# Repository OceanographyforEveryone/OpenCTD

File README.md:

# OpenCTD Rev8 is here!

**The ocean belongs to everyone.** The tools to study the ocean should be accessible to anyone with the curiosity and motivation to pursue that inquiry. Build your own [research-quality oceanographic instrument](https://tos.org/oceanography/article/the-openctd-a-low-cost-open-source-ctd-for-collecting-baseline-oceanographic-data-in-coastal-waters) and let's explore the ocean, together. 

# OpenCTD: Oceanography for Everyone

The CTD is an oveanographic instrument that measures salinity, temperature, and depth. By measuring these
characteristics, scientists can begin to unlock ocean patterns hidden beneath the sea's surface.

CTDs come in a variety of shapes, sizes, and applications. Most oceanographic research vessels have a CTD connected to a rosette platform, which houses other instruments and collects water samples in parallel with real-time data. CTDs are also commonly attached to fixed moorings, autonomous underwater vehicles (AUVs), remote-operated vehicles (ROVs), and even to marine animals.

Unfortunately, commercial CTDs are expensive. The most affordable models cost several thousand dollars. For near-shore oceanographic research on the relatively shallow continental shelf, this cost can be prohibitive. This
effectively excludes formal researchers from low and middle income countries, and small island states. Even in high-income countries, formal researchers at teaching institutions or at early career stages may also find themselves priced out of ocean research. Informal researchers such as citizen oceanographers, educators, conservation and management practitioners and students of all levels face severe challenges accessing expensive scientific instruments. 

**You don’t need to ask for permission to understand your world.**

By building your own instruments to study and understand the natural world, you are expanding the circle of knowledge production. A scientist who can make their own instruments is not beholden to the cycles of funding and access that constrain formal, institutional inquiry. A researcher who can build and repair their own equipment is not dependent on the whims of academic sentiment to decide what is and is not worthy of study. A community leader who has the tools to create their own data does not have to wait for institutions to take notice
of an emerging crisis before taking action. 

.jpg)

### Build Your Own CTD

The OpenCTD is a low-cost, open-source CTD designed for budget-restricted
scientists, educators, and researchers working in nearshore coastal ecosystems.
In these waterways, entire research projects can be conducted for less than the
cost of a commercial CTD. OpenCTD was developed by a core team of marine
ecologists in collaboration with a community of scientists, engineers, makers,
and conservation practitioners from around the world. It is assembled from
components commonly available at large hardware stores or through major online
retailers. An Arduino-based microcontroller controls an array of sensors sealed
within a PVC pipe. Power is provided by a standard 3.7V lithium polymer battery
and data are stored in a tab-delimited text file accessed via SD card.  All
OpenCTD software is released open source with no restrictions on use. 

The OpenCTD built by the end-user, providing both access to
the tools of oceanography as well as the skills to maintain, repair, and
replace OpenCTDs. For scientists working in remote settings, the repairability
of the OpenCTD is intended to prevent equipment failures from spiraling into
project failures. For educators seeking novel, in-depth, hands-on STEM
experience for advanced students, the process of building an OpenCTD offers an
introduction to coding, 3D-printing, hardware prototyping, and electronics.
Construction of an OpenCTD can provide a practical foundation for courses in
oceanography and marine or environmental science. 

# Visit [Oceanography for Everyone](http://oceanographyforeveryone.com/) to learn more, inquire about workshops, or purchase OpenCTD kits!

### Publications

Thaler, A., S.K. Sturdivant, R.Y. Neches, and J.J. Levenson. 2024. [The OpenCTD: A low-cost, open-source CTD for collecting baseline oceanographic data in coastal waters](https://tos.org/oceanography/article/the-openctd-a-low-cost-open-source-ctd-for-collecting-baseline-oceanographic-data-in-coastal-waters#citation). Oceanography 37(2):167–173, https://doi.org/10.5670/oceanog.2024.602.

### Core Resources

The [OpenCTD Construction and
Operation](https://github.com/OceanographyforEveryone/OpenCTD/tree/main/Documentation)
manual provides a comprehensive, step-by-step guide to building your own
OpenCTD, with a standard construction pathway as well as numerous alternatives
depending on parts availability and technical skills. A shorter manual covering just the calibration process is also available. 

The OpenCTD [core software](https://github.com/OceanographyforEveryone/OpenCTD/tree/main/Software) is designed
to be used with an M0-style Arduino microcontroller, for which we recommend the
[Adafruit Adalogger Feather M0](https://www.adafruit.com/product/2796). 

You can find all the Arduino libraries as described in the manual, as well as
software for calibrating the conductivity sensors in
[Support](https://github.com/OceanographyforEveryone/OpenCTD/tree/main/Software/Support).

Hardware file for both 3D printable components and the control unit PBC can be found in [Hardware](https://github.com/OceanographyforEveryone/OpenCTD/tree/main/Hardware)

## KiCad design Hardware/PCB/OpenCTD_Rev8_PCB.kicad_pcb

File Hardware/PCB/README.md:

# OpenCTD PCB

The OpenCTD main board is designed using [KiCad](https://www.kicad.org/).

The current [OpenCTD]() uses the [OpenCTD Rev8 control board](). Previous generation control boards are archived in [Retired](https://github.com/OceanographyforEveryone/OpenCTD/tree/main/Retired). 

The Oceanography for Everyone Custom Pressure Sensor breakout board ([Ofe_CPS](https://github.com/OceanographyforEveryone/OpenCTD/blob/main/Hardware/PCB/OfE_CPS.zip)) allows you to build an inexpensive version of the Sparkfun Breakout Board, but requires advanced soldering techniques.

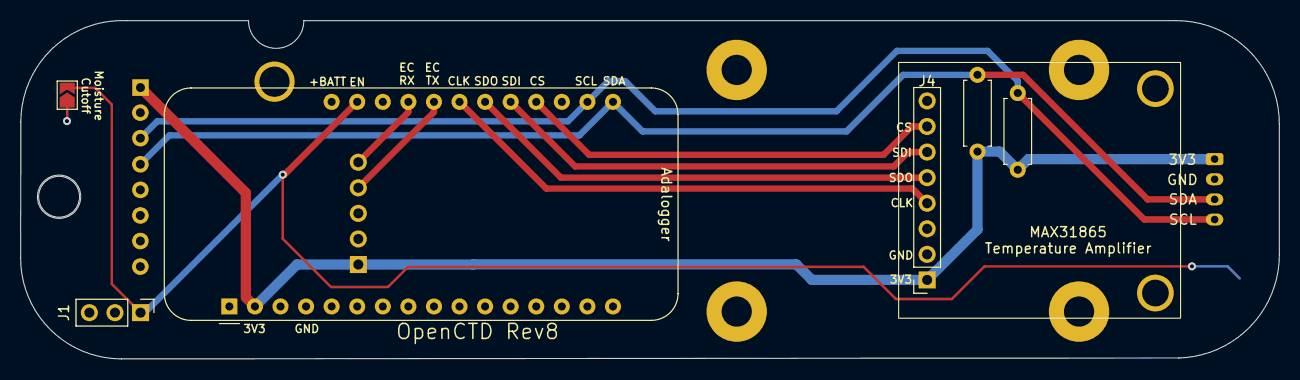
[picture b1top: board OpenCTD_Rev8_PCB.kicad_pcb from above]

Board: 2 copper layers, 125.0 x 33.6 mm, 5 parts (1 on the bottom side), 5 nets.

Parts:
J1: Conn_01x03_Male; PinHeader_1x03_P2.54mm_Vertical
R2, R3: 10k; R_Axial_DIN0207_L6.3mm_D2.5mm_P7.62mm_Horizontal
U1: adafruit_ds3231; Adafruit_DS3231_flipped_noholes
U3: adafruit_feather; Adafruit_Feather_With2MountingHoles

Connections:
+3V3: R2.1, R3.1, U1.1 (Vin), U3.2 (3V3)
EN: J1.1, U3.27 (EN)
GND: J1.2, U1.2 (Gnd), U3.4 (GND), U3.16 (NC)
SCL: R2.2, U1.3 (SCL), U3.18 (SCL)
SDA: R3.2, U1.4 (SDA), U3.17 (SDA)

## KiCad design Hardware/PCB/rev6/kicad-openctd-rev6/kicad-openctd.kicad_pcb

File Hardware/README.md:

# OpenCTD Hardware 

This directory contains hardware files for building the OpenCTD Rev8. The [3D printable shapefiles](https://github.com/OceanographyforEveryone/OpenCTD/tree/main/Hardware/3DPrints) include the PowerSquid protective chassis, the sensor baseplate, and the router jigs and other accessories. The [printed circuit boards](https://github.com/OceanographyforEveryone/OpenCTD/tree/main/Hardware/PCB) include the KiCad and Gerber files for the OpenCTD Rev8 Control Board and the Oceanography for Everyone Custom Pressure Sensor breakout board. 

If you've been lucky enough to recieve Andrew's business card, [Benchtester](https://github.com/OceanographyforEveryone/OpenCTD/tree/main/Hardware/Benchtester) includes instructions for building a working test board for OpenCTD components, though, please note, the Benchtester was designed for the OpenCTD Rev7. 

### Electronics

The OpenCTD is controlled by an [Adalogger Feather M0](https://www.adafruit.com/product/2796) microcontroller development board.

Instructions on how to upload OpenCTD firmware to the microcontroller board can
be found in [Documentation](https://github.com/OceanographyforEveryone/OpenCTD/tree/main/Documentation). General instructions and
learning resources about the Adalogger Feather M0 board itself can be found in the [Adafruit Learning
Guide](https://learn.adafruit.com/adafruit-feather-m0-adalogger/).

The OpenCTD electronics can be assembled using a breadboard, or using a custom PCB. The custom PCB is designed using [KiCad](https://www.kicad.org/), and can be ordered in small batches from many PCB fabrication services around the world using the files located in the [PCB](https://github.com/OceanographyforEveryone/OpenCTD/tree/main/Hardware/PCB) directory.

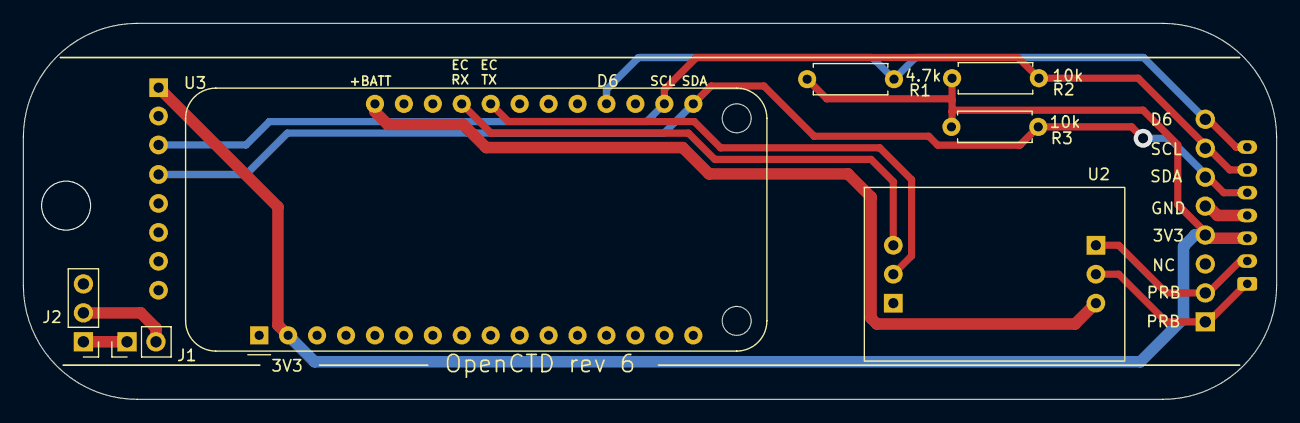
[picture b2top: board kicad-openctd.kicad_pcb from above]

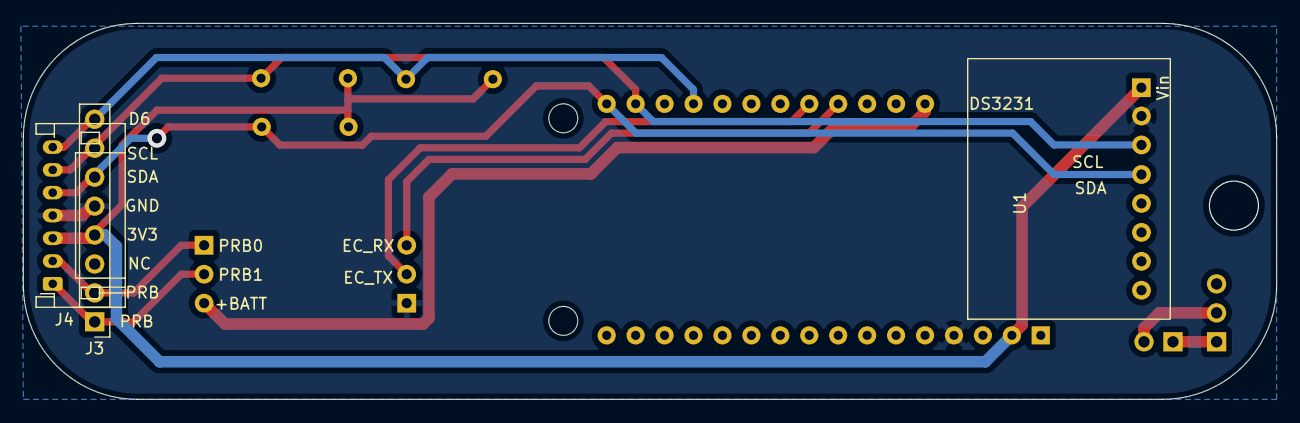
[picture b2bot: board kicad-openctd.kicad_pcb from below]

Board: 2 copper layers, 110.0 x 33.0 mm, 10 parts (3 on the bottom side), 12 nets.

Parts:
J1: Conn_01x02_Male; PinHeader_1x02_P2.54mm_Vertical
J2: Conn_01x03_Male; PinHeader_1x03_P2.54mm_Vertical
J3: RA pin header female; PinHeader_1x08_P2.54mm_Vertical
J4: JST-PH7; JST_PH_S7B-PH-K_1x07_P2.00mm_Horizontal
R1: 4.7k; R_Axial_DIN0207_L6.3mm_D2.5mm_P7.62mm_Horizontal
R2, R3: 10k; R_Axial_DIN0207_L6.3mm_D2.5mm_P7.62mm_Horizontal
U1: adafruit_ds3231; Adafruit_DS3231_flipped_noholes
U2: atlas-ec; Atlas_EC
U3: adafruit_feather; Adafruit_Feather_With2MountingHoles

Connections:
+3V3: J3.4, J4.3, R1.1, R2.1, R3.1, U1.1 (Vin), U3.2 (3V3)
+BATT: U2.6 (Vcc), U3.28 (Bat)
D6: J3.8, J4.7, R1.2, U3.20 (D6)
EC_RX: U2.3 (Rx/SCL), U3.25 (D13)
EC_TX: U2.2 (Tx/SDA), U3.24 (D12)
GND: J3.5, J4.4, U1.2 (Gnd), U2.1 (Gnd), U3.4 (GND)
unnamed: J1.1, J2.1
unnamed: J1.2, J2.2
PRB0: J3.2, J4.2, U2.4 (PRB)
PRB1: J3.1, J4.1, U2.5 (PRB)
SCL: J3.7, J4.6, R2.2, U1.3 (SCL), U3.18 (SCL)
SDA: J3.6, J4.5, R3.2, U1.4 (SDA), U3.17 (SDA)

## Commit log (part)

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2014-04-08 Create Coalescent
2014-04-08 Update Coalescent
2015-08-19 Create OpenCTD_master
2015-08-20 Trivial code cleanup
2015-08-21 Minor code cleanup (Slightly risky)
    Mostly harmless stuff. And this...
    Serial is a singleton, which gets constructed exactly once, in headers somewhere. Since there can be no additional instances, I created a reference to it named monitorSerial. If that line isn't broke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
2015-08-21 Update OpenCTD_master
    Removed unused variables, housekeeping
2015-08-21 Update README.md
    Added pinouts
2015-08-21 Expanded project description in README.md
2015-08-21 Trivial README.md edits
2015-08-21 Omitting Stale Measurements
    Extrapolating possible intent from that "string_received" global before, this patch only prints EC_data values if they were obtained during the current loop() iteration. Otherwise, "---" is logged in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
    .
    .
    Sidenote: ecSerial.readBytesUntil(13, ...) seems fairly safe. It only threatens incomplete reads if you underestimate the max chars per line - or if the device becomes unresponsive until the serial's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
    .
    .
2015-10-13 Added 3D printer file
2015-10-15 Just heaps of data
    Added all data files from the BlueHeron 2015-11 Research cruise on Lake
    Superior, including all raw and processed files pertaining to CTD Casts.
    Need to establish readme regarding this cruise for ease of access.
2015-10-15 Cleaned up CSV files
2015-10-15 Added Notes
    Added handwritten notes from the cruise and changed station folder name.
2015-10-15 Fixed file name
2015-10-15 Create Readme
    With a style guide for starting a field trial
2015-10-16 Added calibration information.
2015-10-16 Build Instructions
2015-10-17 Added Sketchup Files
2016-02-01 Create CODE_OF_CONDUCT.md
    Added contributor code of conduct from http://contributor-covenant.org/.
2016-02-01 Added CoC statement
2016-06-17 Revert "Omitting Stale Measurements"
2016-06-17 Revert to last stable master
2016-06-18 #HackTheOcean Marathon Session
    Code changes, STL fixes, upgrades, glory
2016-06-18 Updated STL files
2016-06-18 Updated software
2016-06-18 Uploaded fresh .ino
2016-06-18 HackTheOcean
2016-06-18 Deconflicted
2016-06-18 Fix STLs
2016-06-18 Added two inch pipe plate
2016-06-19 CTD Code for Qduino
2016-06-19 Updated pinouts
    for qduino software
2016-06-19 added links
2016-06-19 added servoflo to BOM
2016-06-19 added SD card build instructions
2016-06-19 Added pictures for SD card reader instructions.
2016-06-20 updated overview
2016-06-20 update skills needed
2016-06-20 Update project status
2016-06-20 fixing file paths
2016-06-20 Fresh Upload
2016-06-20 Updated BoM
2016-06-20 Updated software lists
2016-06-21 Temp and conductivity
2016-06-21 Updated calibration instructions, almost done!
2016-06-21 potting done
2016-06-21 Done!
2016-07-07 typos
2016-07-20 Uploaded Data
2016-07-20 Updated pressure test
2016-09-06 raw data uploaded
2016-09-06 new folder
2016-09-06 names
2016-09-06 processed data, bad conductivity probe
2016-09-06 hermine 2
2016-09-06 photos
2016-09-06 added photo narrative and lessons learned
2016-09-06 added first look
2017-01-17 Update README.md
    Fixed typos, added notes about sourcing, changed pressure sensor seating instructions
2017-03-30 Updated BoM
    Updated the bill of materials and made it more user friendly.
2017-03-30 Update README.md
    Fixed formatting.
2017-03-30 Update README.md
    Added gripper plug to BoM.
2017-03-30 Update README.md
    Added acrylic tube.
2017-03-30 Update README.md
    fixed typo (Thanks, jlreeve!)
2017-03-30 Update OpenCTD_qDuino.ino
    Added notes.
2017-03-31 Update README.md
    Fixed some typos and added details to intro, BoM, tools
2017-04-05 Temperature
    Added links for Cave Pearl Project about temperature calibration.
2017-04-17 added partners and projects
2017-04-18 Added Qtechknow quick-start guide
2017-04-18 fixed link markdown
2017-05-09 Create Basic RPlotter
2017-05-10 CTDizzleMk3.2
    Now creates a new file on power cycle.
2017-05-20 CTDizzle_Mk3.2
2017-07-17 Removed temperature compensation.
    Latest test shows conductivity measurement issues.
2017-08-04 Added temp test program
2017-08-04 Massive Update with more coming
    Significant changes to the build guide to incorporate new protocols, equipment, and sweet tricks.
2017-08-05 Added data and images from temp test
2017-08-05 spelled "process" correctly
2017-08-28 Added descriptions for field trials.
2017-08-28 Fixed typos and added details to 3D Printed Parts
2017-08-28 upload image
    image.
2017-09-22 Added support for pressure sensor tester
2017-09-22 added note about pressure sensor software
2017-09-22 Created folder for data processing
2017-09-22 Updated pressure test folder
2017-09-22 Updated support code.
2017-09-22 Added conversion template
2017-09-22 Shrunk file
2017-09-23 Updated Field Notes
2017-09-23 Added time constant
2017-09-25 Huge update
    Numerous typos and corrections, updated build guide, replaced amazon links with easier ones to track.
2017-09-25 Update README.md
    updated the "updated" statement
2019-04-22 house cleaning
2019-06-29 Moved older CTD to retired folder
2019-07-05 Added files and images
2019-12-09 Update
    Excel template and standard baseplate
2020-08-27 Format Code (Remove Extra Whitespace)
2020-10-12 Fix EC & Temp Sensor Timing Bug
    Fixes issue that caused EC sensor output to occasionally contain weird characters or miss line-endings. I found this happened when the serial data from the EC sensor happened to come in at the same t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
    Fix:
    1) I moved the temperature measurement steps so they only happen immediately after the EC sends a full measurement back.
    2) use the setWaitForConversion(false) mode in the Dallas Temperature Library so that it can request a temperature
2020-10-12 Now it starts a new data log each time it is powered up
    Big Changes:
    1) Makes a new data log each time it is powered up rather than appending to the old one.
    2) Uses the CSV file format (Comma Separated Values) for easier use in programs like excel and others.
    3) First column contains the Date & Time with a space inbetween (I found Excel & Python parsed this date time format better)
    ^ This is easy to switch back (see the note in the get_date_time_string function)
    Improvements:
2020-10-21 Better serial messages for starting the log
2020-12-01 Update OpenCTD_master_m0.ino
    Missing semicolon.
2020-12-02 Update README.md
    Added project updates
2020-12-07 Update OpenCTD_master_m0.ino
    Split date and time into two columns
2021-12-08 Update README.md
    stakholders -> stakeholders
2022-03-10 restored
2022-03-10 New Chassis
2022-05-03 Create folder for Arduino Libraries
2022-05-03 Added libraries
2022-05-03 Upload compressed libraries to GitHub
2022-05-03 Move EC calibration from standalone folder
2022-05-03 Update README.md
    Added more detail the the readme file.
2022-05-17 Update OpenCTD_ConstructionOperation.pdf
    Fully updated and revised manual
2022-06-03 Added PCB File
2022-06-06 file management
2023-03-17 top-level project reogranization
2023-03-17 update README files
2023-03-17 updates to main README and CODE_OF_CONDUCT
2023-03-17 adding and updating READMEs
2023-03-17 initial Markdown conversion of manual
2023-05-04 Reorganize
    not all 3d print files are for the enclosure
2023-05-04 rename source code
    remove "master" terminology
2023-05-04 rename
2023-05-10 restructured folders for clarity
2023-05-11 Update README.md (#35)
2023-06-12 Calibration protocol update
    complete rewrite of the calibration software for the sole purpose of getting a carriage return between each line.
2023-06-12 Revert "Calibration protocol update"
    This reverts commit 07e96f322140d102123a8a6c9b91f18167ef9273.
2023-06-13 Complete rewrite of Calibration Software
    Ground up rebuild to make it actually user friendly. Now has menu of commands, sets sample rate to zero, and has line breaks for data.
2023-06-13 Updated datalogging
    Changed LOG to CAST in filename and change char* to const char* for C++ compatibility
2023-06-13 Update README.md
    Fixed links and updated text for clarity
2023-06-13 Upgrades to calibration software
    added more descriptive command menu
2023-06-13 Cleaned up data template
    Everyone loves excel, right?
2023-06-13 Update README.md
    Added Google Sheets file
2023-06-14 Rename README.md to OpenCTD_ConstructionOperation.md
2023-06-14 Create OpenCTD_CalibrationDataManagement.pdf
    Added Calibration Guide
2023-06-20 Added temperature readings to calibration code
    Added temperature readings to calibration software
2023-06-26 Create RTC_Reset.ino
    Create a small program to reset the real-time clock
2023-06-27 Update 3D prints
2023-09-28 Update README.md
    spelled salinity correctly after 9 years
2023-12-20 Updated New Manual
2024-01-01 Added gitignore.
    Added line for PyCharm output.
2024-01-01 Python Example for importing and plotting a single profile OpenCTD file.
    This example takes a CSV file and converts data to an Xarray Dataset object. Three helper functions are added.
    - import_file ingests a CSV file from a given filepath.
    - process_data computes additional data products like sea_water_practical_salinity and sea_water_density using the Gibbs-Seawater python package.
    - split_cast will split a cast into down/up using the max depth.
    Data are not cleaned in anyway. Future updates should consider implementing the gross range test for each variable before the additional data products are computed.
2024-04-10 update 3D printer files
2024-04-10 added router jigs
2024-04-10 add power management upgrade
2024-04-10 added new control board
2024-08-16 EZO LED
    Added code to allow users to turn the Atlas EZO LED indicator light on or off to preserve power
2024-08-27 Added code to run the 5803-14ba pressure sensor in circuitpython
2026-06-17 Added Rev8 3D prints
2026-06-17 moved PCB files
2026-06-18 Added 3 more files
2026-06-18 Moved old CTDs to retired
2026-06-18 added PCB
2026-06-18 update gerbers
2026-06-18 Added OfE_CPS
2026-06-18 moved old documentation to retired
2026-06-18 moved source code to retired
2026-06-18 reorganized documentation
2026-06-18 Added updated software
2026-06-18 Fix Calibration program to work with new temperature
2026-06-18 Added a Python notebook for importing and plotting OpenCTD data files. (#36)
    * Added gitignore.
    Added line for PyCharm output.
    * Python Example for importing and plotting a single profile OpenCTD file.
    This example takes a CSV file and converts data to an Xarray Dataset object. Three helper functions are added.
    - import_file ingests a CSV file from a given filepath.
    - process_data computes additional data products like sea_water_practical_salinity and sea_water_density using the Gibbs-Seawater python package.
